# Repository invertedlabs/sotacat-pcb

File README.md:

# SOTAcat PCB

This project creates a SOTAcat PCB designed in [KiCad](https://www.kicad.org) and compatible with Brian AB6D's [SOTAcat](https://github.com/SOTAmat/SOTAcat) and [SOTAMAT](https://sotamat.com/) ("SOTA-Mate") web service and software. Brian provides a cloud service and iOS and Android which can interface with SOTAcat hardware to command an Elecraft KX2 or KX3 to transmit SOTA or POTA spots from the field via the FT8 spotting networks.  [The SOTAcat software](https://github.com/SOTAmat/) by Brian and Jeff KC6X also has other great features like a web interface that polls SOTA and POTA spots from their respective databases and commands the KX2 or KX3 to the spot frequency and mode with a single click.

This repository contains hardware files only. These files are available in zipped gerber form under "releases" which can be uploaded to PCB board manufacturers like [OshPark](https://www.oshpark.com), [JLCPCB](https://www.jlcpcb.com), or [PCBWay](https://www.pcbway.com) for quick turn around prototype-quantity builds.

# Attribution

A lot of folks from the SOTA community have contributed to this project.  For full attribution, see [the attribution list](https://github.com/SOTAmat/SOTAcat?tab=readme-ov-file#attribution) in the software repository. 

Specifically, this project wouldn't have been possible without the great SOTAmat software and original SOTAcat concept by Brian Mathews AB6D, the SOTAcat software authored primarily by Brian and Jeff Kowalski KC6X, and timely feedback from Brian, Jeff, and Rex Vokey KE6MT during the hardware design phase.

# Bill of Materials

A full BOM will be uploaded in due time, for now, refer to the schematic documents for build information, including part numbers for ordering from suppliers like [DigiKey](https://www.digikey.com) or [Mouser](https://www.mouser.com).

# Batteries

SOTAcat is a battery powered device. The battery is charged via a USB-C port.  Under the hood, a Seeeed XIAO ESP32-C3 board provides the USB port and battery charging circuitry. The battery is charged at 350mA, which limits the battery selection to batteries that can safely accept this amount of current. Most single-cell batteries above 300mAh will do fine given the bettery isn't allowed to overheat when charging. While many LiPo batteries are limited to 1C charging, test show that with a 300mAh battery the time spent above 1C is very brief, generally less than 10 minutes with a fully dead battery. Even so, the PCB can get warm during the charging process, and steps should be made to keep the battery and PCB cool during charging. This can be done by keeping the thermal paths between the PCB and the battery to a miniumum (e.g. don't tape them directly together without an insulating layer), and only charging an enclosed device at room temperature (<80 deg F, or <27 deg C).  

As with all LiPo batteries, *always monitor the device while charging* and don't leave the device charging in very hot conditions such as a car on a warm day.

More information will be forthcoming about which batteries we have tested and recommend. If purchasing a battery, connectors have been provided on v0.3 for both TinyCircuits batteries and KBT batteries. Check the schematic and layout for pinout information.

# Antenna

A wifi antenna needs to be attached to the XIAO ESP32-C3 module using the U.FL connector on that PCB (between the buttons).  Most XIAO ESP32-C3 purchases will include a flexible WiFI antenna. Other antennas have been tested and may be preferable in some cases (like when using a 3D printed case). Specifics TBD. 

# 3D Printed Cases

A number of 3D printed cases have been developed alongside this hardware by Justin K5EM (@poyting).  These files will also be posted and made available in time. If you want to build one before this happens, just reach out to @poynting.

# Changelog

v0.3 updates:
* Move the serial TX pin to the KXx interface to a pin without bootloader messages.
* Add transistor-based level conversion / inversion to the serial lines in both directions, improving robustness of the serial communications and removing the need for software serial port inversion.
* Add a battery monitor IC with a coulomb counter to improve the robustness of the battery level indicator. This is active even with the power switch off and causes ~5uA of battery drain. 
* Change form factor slightly by moving KXx plug to the corner of the board. This opens up room on the KX2 so that the SOTAcat doesn't block the key port in most cases.

v0.2 was a very quick turn PCB that translated AB6D's schematic to a PCB. v0.2 has some issues, notably that the TRRS R2 and Shield pins need to be tied together for working serial, and EFUSEs need to be set on the XIAO ESP32-C3 to limit the debug output on the pin used for KXx serial communications. With these changes, the device is very functional.

# Warranties (and lack thereof)

No warranties are expressed or implied by Jutin McAllister or InvertedLabs, LLC for the hardware in this repository. All files and information are provided as is, with all faults, and may not be suitable for any purpose.  While a best-faith effort has been taken to test these designs, they may cause damage to connected equipment. Some designs may be untested, and may not work as provided. Lithium batteries are inherently dangerous and may cause personal injury and/or damage to property, even when used correctly. Always monitor batteries during charging and usage, and store batteries safely per the battery manufacturer's recommendations. Never charge batteries unattended, while sleeping, or when hot. If you're not comfortable, your batteries aren't comfortable. Proceed with caution, use at your own risk.

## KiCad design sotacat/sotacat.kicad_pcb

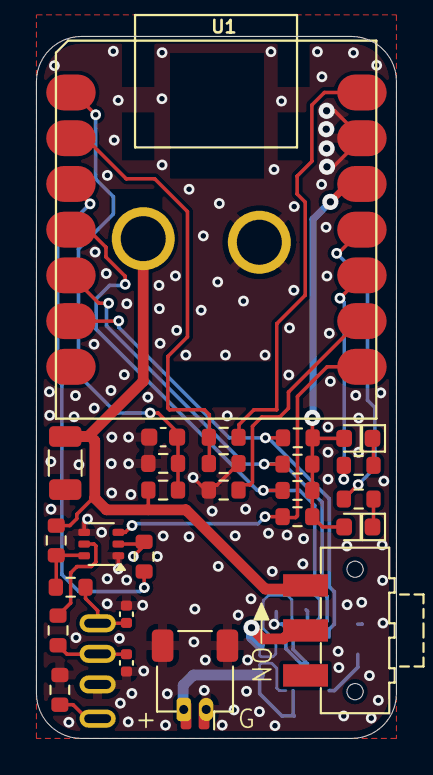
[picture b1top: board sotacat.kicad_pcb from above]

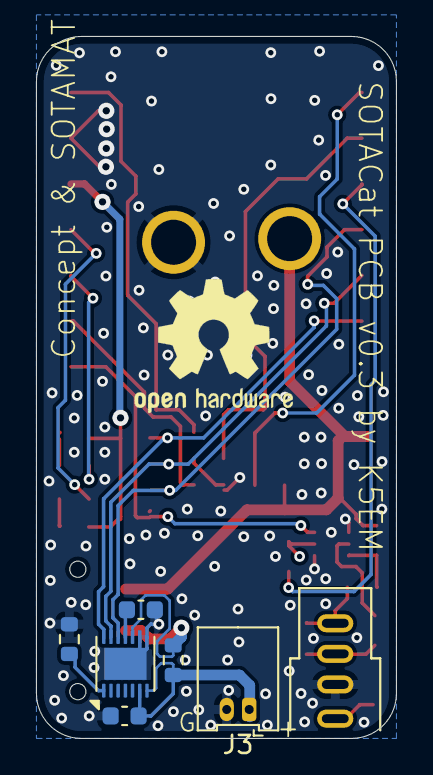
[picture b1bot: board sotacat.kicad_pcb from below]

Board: 2 copper layers, 20.0 x 39.0 mm, 33 parts (7 on the bottom side), 26 nets.

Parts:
C1: 22uF; C_1206_3216Metric
C2, C3: 0.1uF; C_0603_1608Metric
C4: 0.47uF; C_0603_1608Metric
C5, C6: 30pF; C_0402_1005Metric
D1: AMBER; LED_0603_1608Metric
D2: BLUE; LED_0603_1608Metric
J1: 54-00035; TENSILITY_54-00035
J2: JST-SH; JST_SH_SM02B-SRSS-TB_1x02-1MP_P1.00mm_Horizontal
J3: PicoBlade; Molex_PicoBlade_53048-0210_1x02_P1.25mm_Horizontal
Q1: MBT3904DW1; SOT-363_SC-70-6
R1, R2, R8: 200k; R_0603_1608Metric
R3, R5, R11, R12: 10k; R_0603_1608Metric
R4, R13, R14, R15: 4.7k; R_0603_1608Metric
R6, R17: 130; R_0603_1608Metric
R7: 10; R_0603_1608Metric
R9: 100k; R_0603_1608Metric
R10: 0; R_0603_1608Metric
R16: 10m; R_0603_1608Metric
SW1: SW_SPDT; SW_SPDT_CK-JS102011SAQN
TH1: 10k NTC; R_0603_1608Metric
U1: MOUDLE-SEEEDUINO-XIAO-ESP32C3; MOUDLE14P-SMD-2.54-21X17.8MM-VBAT
U3: MAX17260xxTD; TDFN-14-1EP_3x3mm_P0.4mm_EP1.78x2.35mm

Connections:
3V3: D1.2 (A), D2.2 (A), R3.2, R13.1, R14.1, R15.1, U1.12 (3V3)
5V: R9.1, U1.14 (5V)
/BAT_SENSE: C2.1, R1.2, R2.1, U1.1 (PA02_A0_D0)
/I2C_SCL: R14.2, U1.6 (PA9_A5_D5_SCL), U3.14 (SCL)
/I2C_SDA: R15.2, U1.5 (PA8_A4_D4_SDA), U3.13 (SDA)
/K_RX_SC_TX: R5.2, U1.3 (PA10_A2_D2)
/K_TX_SC_RX: Q1.3 (C2), R3.1, U1.8 (PB09_A7_D7_RX)
/R1_KX_TX: C6.1, J1.R1, R12.2
/TIP_KX_RX: C5.1, J1.T, R17.2
/USB_DETECT: R8.1, R9.2, U1.2 (PA4_A1_D1)
/VBAT_RAW: C3.1, J2.2, J3.1, R16.1, U3.6 (BATT), U3.7 (CSN)
/VBAT_SENSE: R16.2, SW1.2 (B), U3.10 (CSPH)
/VREG: C4.1, U3.11 (REG)
/VTH: TH1.1, U3.1 (TH)
/nALRT: R13.2, U1.4 (PA11_A3_D3), U3.12 (ALRT)
/nDIS_BL_MSG: R4.1, U1.9 (PA7_A8_D8_SCK)
/nLED_AMB: R6.2, U1.10 (PA5_A9_D9_MISO)
/nLED_BLU: R7.2, U1.11 (PA6_A10_D10_MOSI)
GND: C1.2, C2.2, C3.2, C4.2, C5.2, C6.2, J1.R2, J2.1, J2.MP, J3.2, Q1.1 (E1), Q1.4 (E2), R2.2, R4.2, R8.2, R10.2, TH1.2, U1.13 (GND), U3.8 (GND), U3.9 (CSPL), U3.15 (PAD)
unnamed: D1.1 (K), R6.1
unnamed: D2.1 (K), R7.1
unnamed: J1.S, R10.1
unnamed: Q1.2 (B1), R5.1
unnamed: Q1.6 (C1), R11.1, R17.1
unnamed: Q1.5 (B2), R12.1
VBAT: C1.1, R1.1, R11.2, SW1.3 (C), U1.15 (VBAT)

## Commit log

2024-02-06 Initial commit as built rev 0.2
2024-02-06 v0.3 placement
2024-02-13 Just playing around with some v0.3 thoughts.
2024-03-08 Add .gitignore
2024-03-08 Updates for Rev0.3. Breaking pin changes.
2024-04-05 PCB v0.3. Added MAX17260xxTD battery monitor, moved plug to corner, moved switch and LEDs accordingly. Changed pinout. Pinout not compatible with v0.2 due to TX data swap to avoid bootloader output.
2024-04-05 v0.3 after closing project.
2024-04-05 Create LICENSE
